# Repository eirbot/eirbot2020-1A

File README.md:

# EIRBOT 2020-1A : Equipe EIRBOAT 

---

Résultat de l'équipe à l'édition d'octobre 2020 : 24 ième / 51
---

Ceci est le dépôt de l'équipe de 1A de l'association de robotique Eirbot. La
description de l'avancement des différents projets est disponible via la 
[descrition](https://github.com/eirbot/eirbot2020-1A/blob/master/description/descrption.pdf) de nos projets. Le projet se divise en plusieures catégories allant du plus bas au plus au niveau (en terme de raprochement avec le côté physique). 

## Membres
Ce projet est réalisé par les différents membres de Eirbot en première année : 
- Alberty Maxime (SEE)
- Barrais Marius
- Camberlin Erwann (Matmeca)
- Delpeuch Sébastien (Informatique)
- Mangin Lucas
- Moroy Liam
- Neveu Emile
- Pouget Filipe
- Poupon Julien
- Savary Clément (SEE)
- Vaquori Yohann
- Vidal Martin

## Installation 
Le projet est construit avec Cmake, il suffit donc de cloner le projet puis 

```
cd eirbot2020-1A/code/
cd build/
cmake .. 
```

## Éxecution 

Depuis le dossier `build/`

Pour compiler le projet il suffit de faire `make project` en ayant un compilateur
de C++.

Plusieurs méthodes permettent d'exécuter le projet.

En local un `./project` suffit, si la nucléo est branchée via le port USB une
simulation de communication est enclenchée (la nucléo renvoie toujours vrai à
chaque demande). Cela peut demander de faire la commande en super utilisateur ou
changer le chemin d'accès au port USB (ligne 110 de ce
[code](https://github.com/eirbot2020-1A/tree/master/code/rasp/src/main.cc)). 

Pour mettre le projet sur la rasp et donc le robot il faut être connecté au même
wifi que la raspeberry puis faire un `make final`.

En plus de l'exécution des tests sont effectués sur les codes, ils peuvent être
compilés en faisant `make test` puis `./test`. A partir de ce moment des tests
sur tous les modules implémentés sont exécutés, le coverage actuel est de 87%

Finalement un `make doc` permet d'afficher la documentation de nos codes.
Elle est de plus disponible sur notre [page web](https://eirbot.github.io/eirbot2020-1A/md__r_e_a_d_m_e.html)

## Description du projet 
### Mécanique
La mécanique du projet se base sur une architecture octogonale structuré par des
profilés avec la notion d'étage. 

### Alimentation 
Un autre étape cruciale de notre robot est la distribution de l'énergie dans ce dernier. Pour ce faire nous passons via une carte d'alimentation, so rôle est de distribuer aux différentes instances l'énergie nécessaire pour fonctionner. 

### Actionneur
Pour réaliser les différentes actions nous avons besoins de différents
actionneurs. 

Tout d'abord des actionneurs simples utiles pour activer le phare et les manches
à air, ils sont au nombre de deux pour gérer facilement chaque côté de la table.

Ensuite un actionneur représentant le pavillon et permettant de lever le
drapeau.

### Puissance 
Une fois que nous pouvons alimenter tous les composants de notre robot nous devons encore permettre un contrôle de la puissance fournie au moteur, pour cela nous créons deux cartes possédant un pont en H, cela nous permet de délivrer la puissance nécessaire à nos moteurs pour nos robots.

### Asservissement
L'idée maintenant que nous avons une mécanique propre, nos différents modules aliméntés et que nous pouvons contrôler précsiement nos moteurs est de créer un asservissement. Le but de l'[asservissement](https://github.com/eirbot/eirbot2020-1A/tree/master/code/nucleo) est de récupérer les informations des encodeurs et de permettre au robot d'atteindre une certainne position tout en gérant l'angle, la puissance des moteurs etc.

### Stratégie
Maintenant que nous avons un asservissement nous devons réaliser les choix pour
notre stratégie. 

La stratégie se décompose en deux parties. Une partie sur la nucléo contenant
les actions "matérielles" à faire (par exemple tourner le servomoteur de
l'actionneur pour la phare). Et une partie de stratégie plus abstraite sur
raspeberry. 

La partie abstraite a plusieurs rôles 
+ Elle contrôle le déroulement de la partie (initialisation, ordre des actions,
  demandes de déplacements ...)
+ Elle gère la communication avec la balise lisant la boussole et le phare 
+ Elle est la seule à connaître la disposition de la table (disposition des
  obstacles, place des ecocups initialement)
+ Elle est capable de calculer une trajectoire entre les obstacles (via un
  algorithme de pathfinding l'A*)
+ Elle est capable de définir dans quel sens il faut ramasser les ecocups
  (probleme du voyageur de commerce, algorithme des colonies de fourmis)
  
Les codes sont disponibles
[ici](https://github.com/eirbot/eirbot2020-1A/tree/master/code/rasp/src). 

### Protocole de communication

Comme dit précédemment nous avons séparé la partie d'implémentation du contrôle
physique (sur la nucléo) et la partie d'implémentation de la stratégie (sur la
rasp). Cela implique donc une communication entre les deux cartes. L'idée est
d'utiliser un protocole de communication du type maitre esclave. Par exemple
lorsque la rasp a trouvé la trajectoire demandé, elle fournit au fur et à mesure
les coordonnées qu'elle souhaite atteindre à la nucléo. Cette dernière via
l'asservissement déplace le robot à la position souhaitée, elle a un certains
temps pour le faire. Si elle arrive à la position demandée elle renvoie "OK", si
elle n'y arrive pas automatiquement le protocole renvoie "TIMEOUT". Si les GP2,
reliés à la nucléo détectent un robot ennemi pendant le déplacement, la nucléo
stoppe le robot et renvoie "DETECTION" à la rasp. Cette dernière prendra alors
les mesures nécessaires pour éviter le robot. C'est ainsi que se déroule la
communication entre la rasp et la nucleo. 

## Phare
En marge du robot nous devons réaliser l'expérience. L'objectif du phare est de se déployer pendant le match pour permettre d'atteindre une certainne hauteur. Cela est réalisé par un bras robotique imprimé en PLA. Ce dernier possède un design comme suit.

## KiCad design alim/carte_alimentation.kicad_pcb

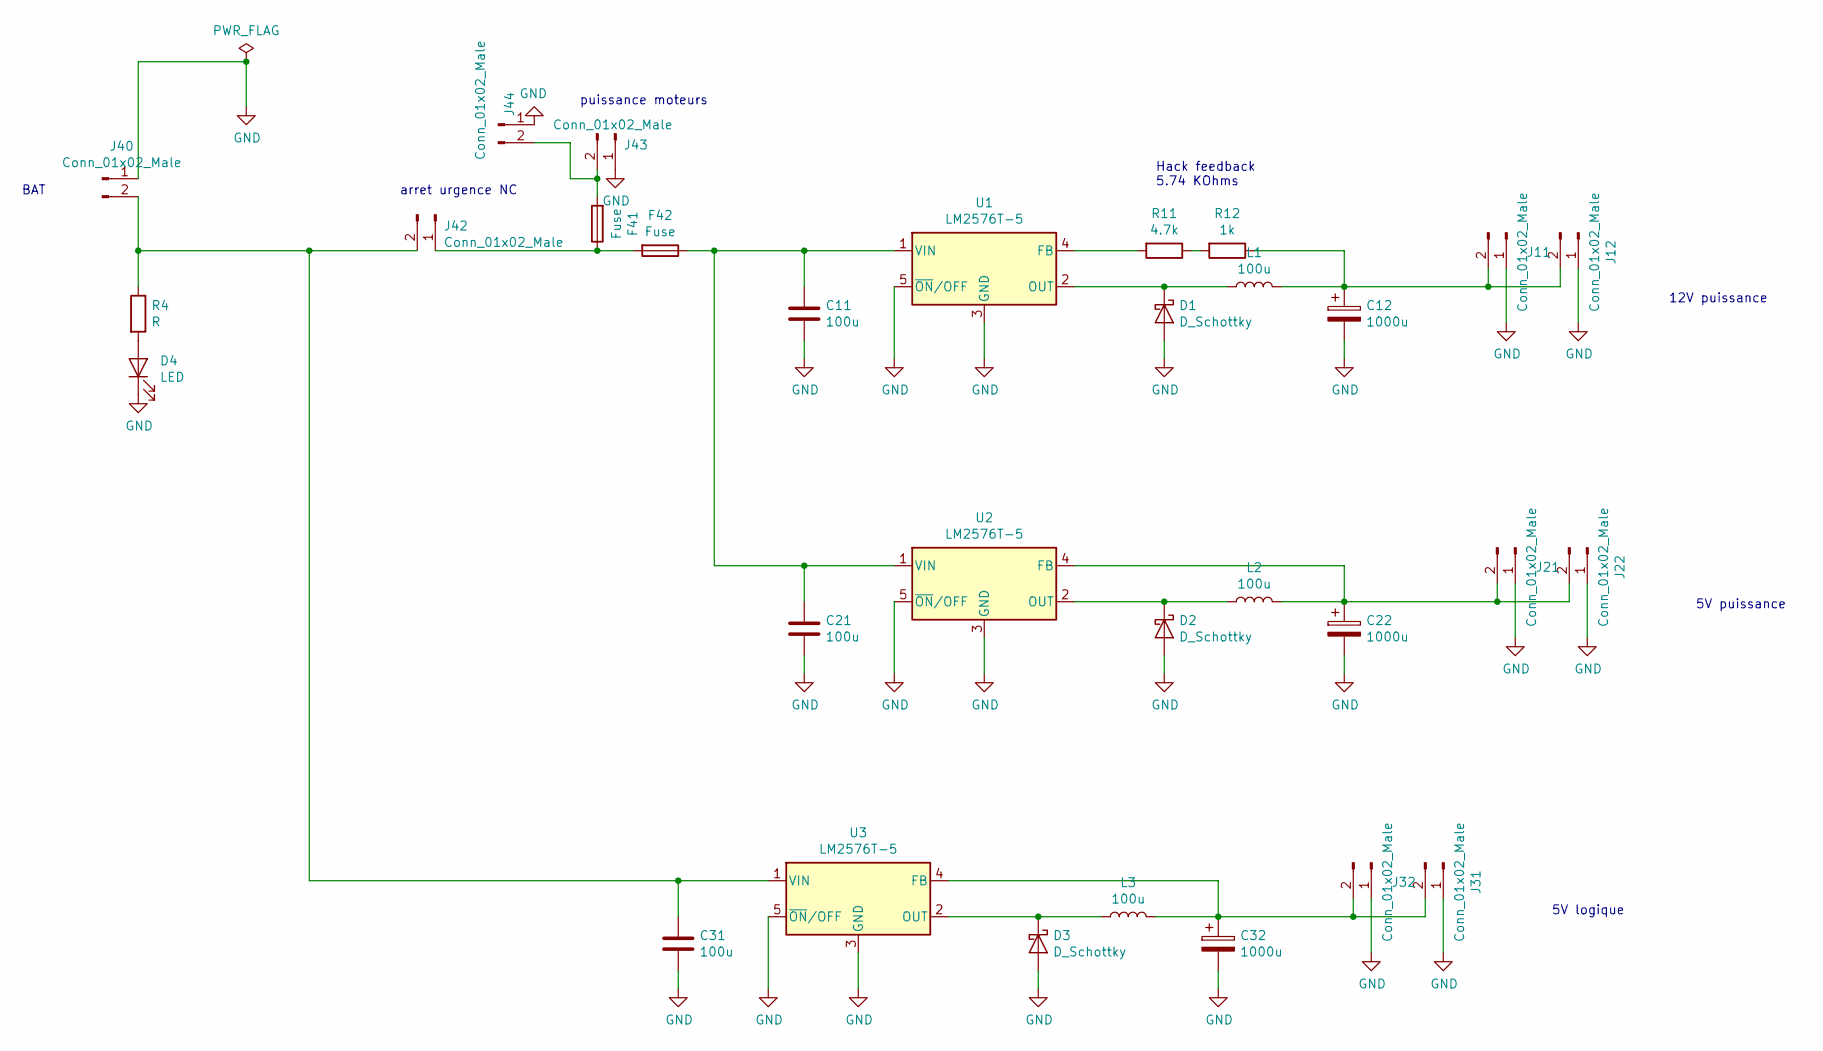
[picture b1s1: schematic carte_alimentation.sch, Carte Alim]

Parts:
C11, C21, C31: 100u; CP_Radial_D10.0mm_P5.00mm
C12, C22, C32: 1000u; CP_Radial_D10.0mm_P5.00mm
D1, D2, D3: D_Schottky; D_DO-27_P12.70mm_Horizontal
D4: LED; LED_D3.0mm
F41, F42: Fuse; fusible_alim
J11, J12, J21, J22, J31, J32, J40, J42, J43, J44: Conn_01x02_Male; TerminalBlock_bornier-2_P5.08mm
L1, L2, L3: 100u; L_Toroid_Vertical_L24.6mm_W15.5mm_P11.44mm_Pulse_KM-4
R4: R; R_Axial_DIN0411_L9.9mm_D3.6mm_P5.08mm_Vertical
R11: 4.7k; R_Axial_DIN0411_L9.9mm_D3.6mm_P12.70mm_Horizontal
R12: 1k; R_Axial_DIN0411_L9.9mm_D3.6mm_P12.70mm_Horizontal
U1, U2, U3: LM2576T-5; TO-220F-5_P3.4x2.06mm_StaggerEven_Lead1.86mm_Vertical

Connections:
GND: C11.2, C12.2, C21.2, C22.2, C31.2, C32.2, D1.2 (A), D2.2 (A), D3.2 (A), D4.1 (K), J11.1, J12.1, J21.1, J22.1, J31.1, J32.1, J40.1, J43.1, J44.1, U1.3 (GND), U1.5 (~ON~/OFF), U2.3 (GND), U2.5 (~ON~/OFF), U3.3 (GND), U3.5 (~ON~/OFF)
unnamed: C11.1, C21.1, F42.1, U1.1 (VIN), U2.1 (VIN)
unnamed: C12.1, J11.2, J12.2, L1.2, R12.1
unnamed: C22.1, J21.2, J22.2, L2.2, U2.4 (FB)
unnamed: C31.1, J40.2, J42.2, R4.1, U3.1 (VIN)
unnamed: C32.1, J31.2, J32.2, L3.2, U3.4 (FB)
unnamed: D1.1 (K), L1.1, U1.2 (OUT)
unnamed: D2.1 (K), L2.1, U2.2 (OUT)
unnamed: D3.1 (K), L3.1, U3.2 (OUT)
unnamed: D4.2 (A), R4.2
unnamed: F41.1, F42.2, J42.1
unnamed: F41.2, J43.2, J44.2
unnamed: R11.1, R12.2
unnamed: R11.2, U1.4 (FB)

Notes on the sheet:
5V logique
5V puissance
12V puissance
BAT
arret urgence NC
puissance moteurs
Hack feedback 5.74 KOhms

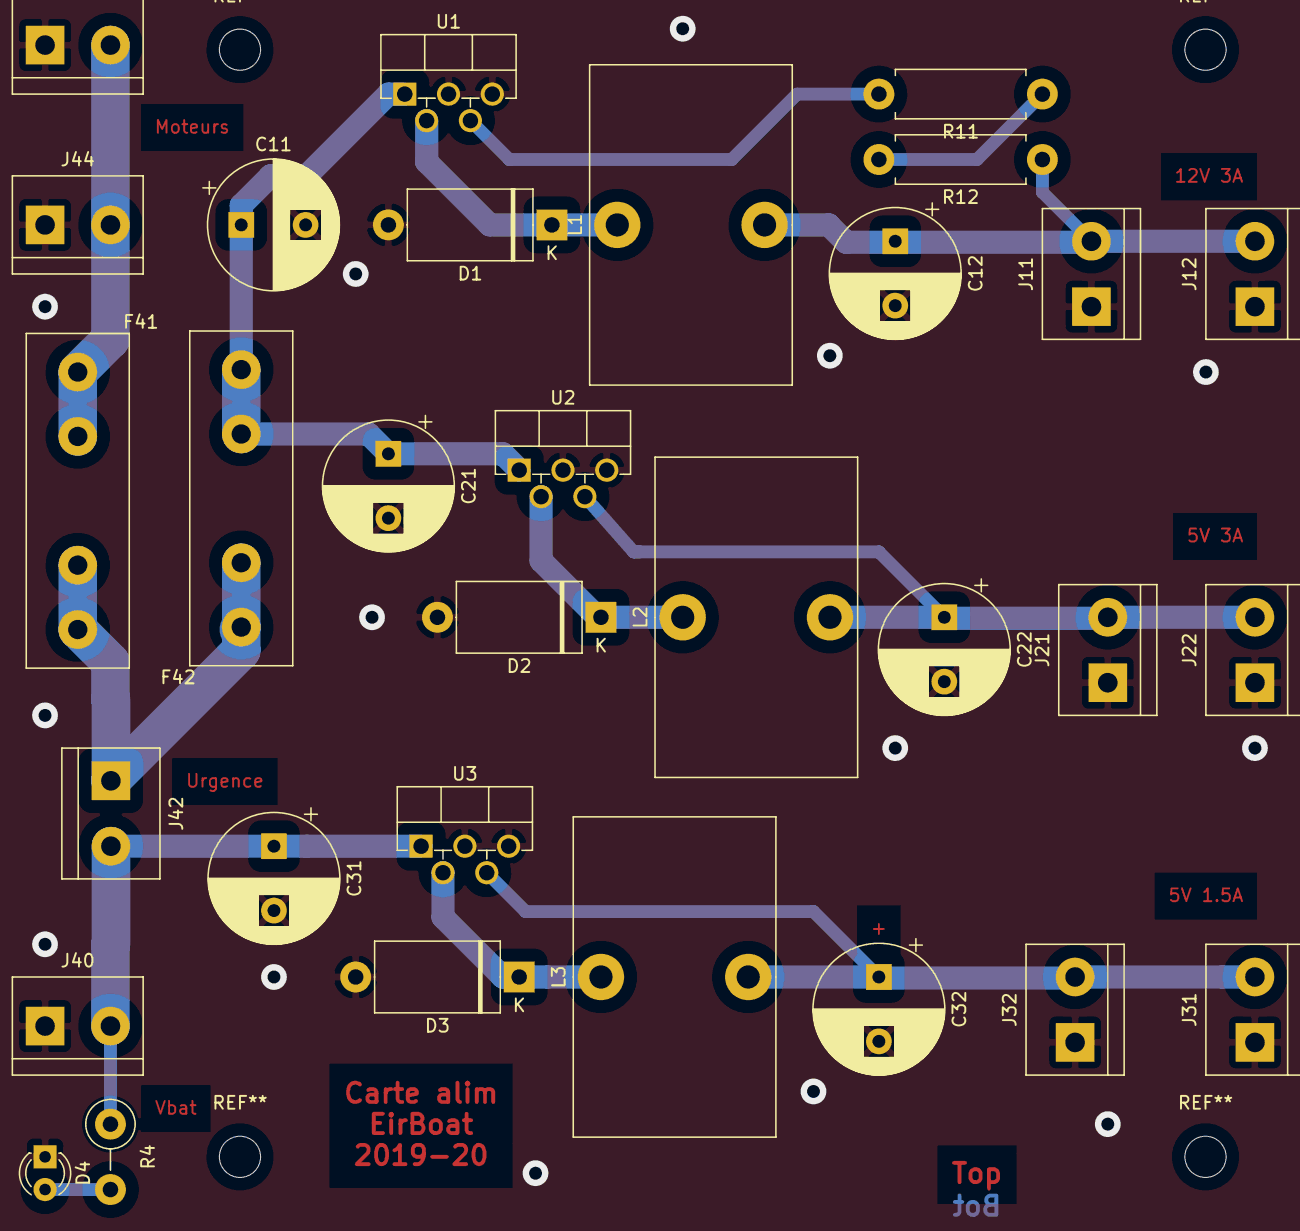
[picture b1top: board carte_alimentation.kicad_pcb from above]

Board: 2 copper layers, 31 parts (0 on the bottom side), 14 nets.

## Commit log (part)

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2020-09-26 fix indentation
2020-09-26 penser bete fonction poll
    la fonction poll risque de tout bloquer ouiiii
2020-09-26 ménage
2020-09-26 add logo
2020-09-27 doing some shit
2020-09-27 ajout test gp2
    lecture tension
2020-09-28 ecriture fonction XY vers coordonnees asserv
    attention aux unites
2020-09-28 Deso pas deso
2020-09-28 calcul angle du robot avec changement de sens de marche
2020-09-29 début séparation en fichier
2020-09-29 doing some shit with files
2020-09-29 separation en fichier ca compile
2020-09-29 consigne
2020-09-30 deplacement fichier dans lib/Asserv
    vrai reset angle et distance
2020-10-01 deploy: 0439d63897e77695bae5679ea3ef1184be37234f
2020-10-01 modif clément
    feedback asserv
    angle et distance absolue
2020-10-04 back to school debug
2020-10-04 tentative position absolue
    a tester
2020-10-05 changement correction encodeur
2020-10-06 correction feedback
2020-10-06 vers l'absolu et l'au-dela !
    des coordonnées qui fonctionnent ça serait mieux
2020-10-07 coordonnees absolues fonctionnelles
2020-10-07 asserv du tonnerre clément
2020-10-09 les memes unités c'est mieux
    go_XY ça marche <3 (tests complémentaires)
2020-10-09 test asserv + XY
2020-10-10 goXY approximatif
    on peut envoyer des commandes du protocole
    feedback protocole a faire
2020-10-11 it... works ?
    SPO, SRO, GPO fonctionnels mais pas hyper précis
2020-10-12 setup cmake crosscompilation
    correction Cmakelists
    creation d'un fichier pour setup la toolchain de cross compilation
2020-10-12 changement timeout test protocole
2020-10-12 creation Readme crosscompilation
2020-10-12 modif readme
2020-10-13 maj test
2020-10-13 add tool
2020-10-13 Add delete
2020-10-14 debug protocole rasp
2020-10-14 supression commentaire inutile
2020-10-14 future debug
2020-10-14 retrait execution automatique apres upload
2020-10-14 correction angle -180
2020-10-14 define debug
2020-10-14 asserv nouveaux coeffs angle
2020-10-15 pavillon
2020-10-15 protocole qui marche (fiable?)
2020-10-15 petite modif asserv
2020-10-15 test protocole carré
2020-10-15 fix timeout
2020-10-15 retrait debug proto oui
2020-10-15 retrait debug proto
2020-10-16 deploy: 4fd4411fbace096ade4191775fe29aa757a17b6c
2020-10-16 Init strat
2020-10-16 activation asserv quand STOP
2020-10-16 retour asserv lente
2020-10-16 Ok set pos
2020-10-16 Revert "retrait debug proto oui"
    This reverts commit 070f2f7ed580a8e94b61b65fb9e6d5b17a70af4b.
2020-10-16 Revert "activation asserv quand STOP"
    This reverts commit e8759eaa4ca1ffa40991fbcdc28772d4c733df69.
2020-10-16 fix id actionneur
2020-10-16 petit fix protocole
    rallongement timeout test
    retrait debug proto rasp
2020-10-17 diminution vitesse et timeout cote nucleo
2020-10-17 fix updatebuffer
    on arrive a lire les données et timeout correctement
2020-10-17 fix seb
2020-10-17 ajout reglage coeff asserv angle protocole
    SKAki,kp,kd
2020-10-17 miaou
2020-10-18 mr proper main
2020-10-18 new time and refresh detect
2020-10-18 fix some minors problems
2020-10-19 tentative limitation acceleration
2020-10-19 tmp debug
2020-10-19 goto chut
2020-10-20 add pypath
2020-10-20 Testing version ok x86
2020-10-21 MAJ time
2020-10-21 limit acceleration
2020-10-21 limite acceleration
2020-10-21 new asserv
2020-10-21 create low level
2020-10-21 asserv activé quand statique
2020-10-21 Add GPIO
2020-10-21 add parse opt usage : ./bin/project -p 1 si on est sur un pc
2020-10-22 add lowlevel & modif main => stable version ??
2020-10-22 refactor test
2020-10-22 deplacement offset dans asserv_vitesse_angle
2020-10-22 fix offset pwm quand negatif
2020-10-22 asserv stable
    pas asservi quand on est arreté
2020-10-22 fix asserv offset
2020-10-22 commande offset asset
2020-10-22 oups fix retrait offset set_pwm lol
2020-10-23 mr proper
2020-10-23 add test low level
2020-10-23 v stable
2020-10-24 fix led jaune
2020-10-24 augmentation timeout nucleo 20s
2020-10-25 fix warning timeout
2020-10-25 init x0 y0
    pour le changement de coté
    maintenant la première commande SPOx,y recue apres un RESET set
    le x0 y0 du robot
2020-10-25 add gp2 test
2020-10-25 add init
2020-10-25 maj meca
2020-10-25 fix init
2020-10-25 fix premiere commande SPOx0,y0
2020-10-25 add pin et fonctions pwm bras
2020-10-26 Livraison Final Balise
    Nouvelle (et dernière) version du code balise avec communication vers la nano-arduino qui envoi le signal au robot.
2020-10-27 stable sans GP2
2020-10-27 debug GP2
2020-10-27 fix actionneur
2020-10-27 add detection strat
2020-10-27 stop quand detection avant
2020-10-27 fix duree pavillon
2020-10-27 creation process_GP2
    ignore les obstacles en dehors de la table et du bord de la table
2020-10-27 disactivate gp2
2020-10-27 add reactivate
2020-10-27 test 3
2020-10-27 lissage GP2
2020-10-27 add compteur
2020-10-28 add meca
2020-10-28 add test score
2020-10-28 serial compteur ntm
2020-10-28 score et actionneur plus bas
2020-10-29 calib blue
2020-10-29 actionneur redroit
2020-10-29 mode panic asserv
    recule de 3 cm
2020-10-31 deploy: 638dc5457b9ce90a69e2c219e3ec328cb3fad7b7
2020-11-01 maj readme
